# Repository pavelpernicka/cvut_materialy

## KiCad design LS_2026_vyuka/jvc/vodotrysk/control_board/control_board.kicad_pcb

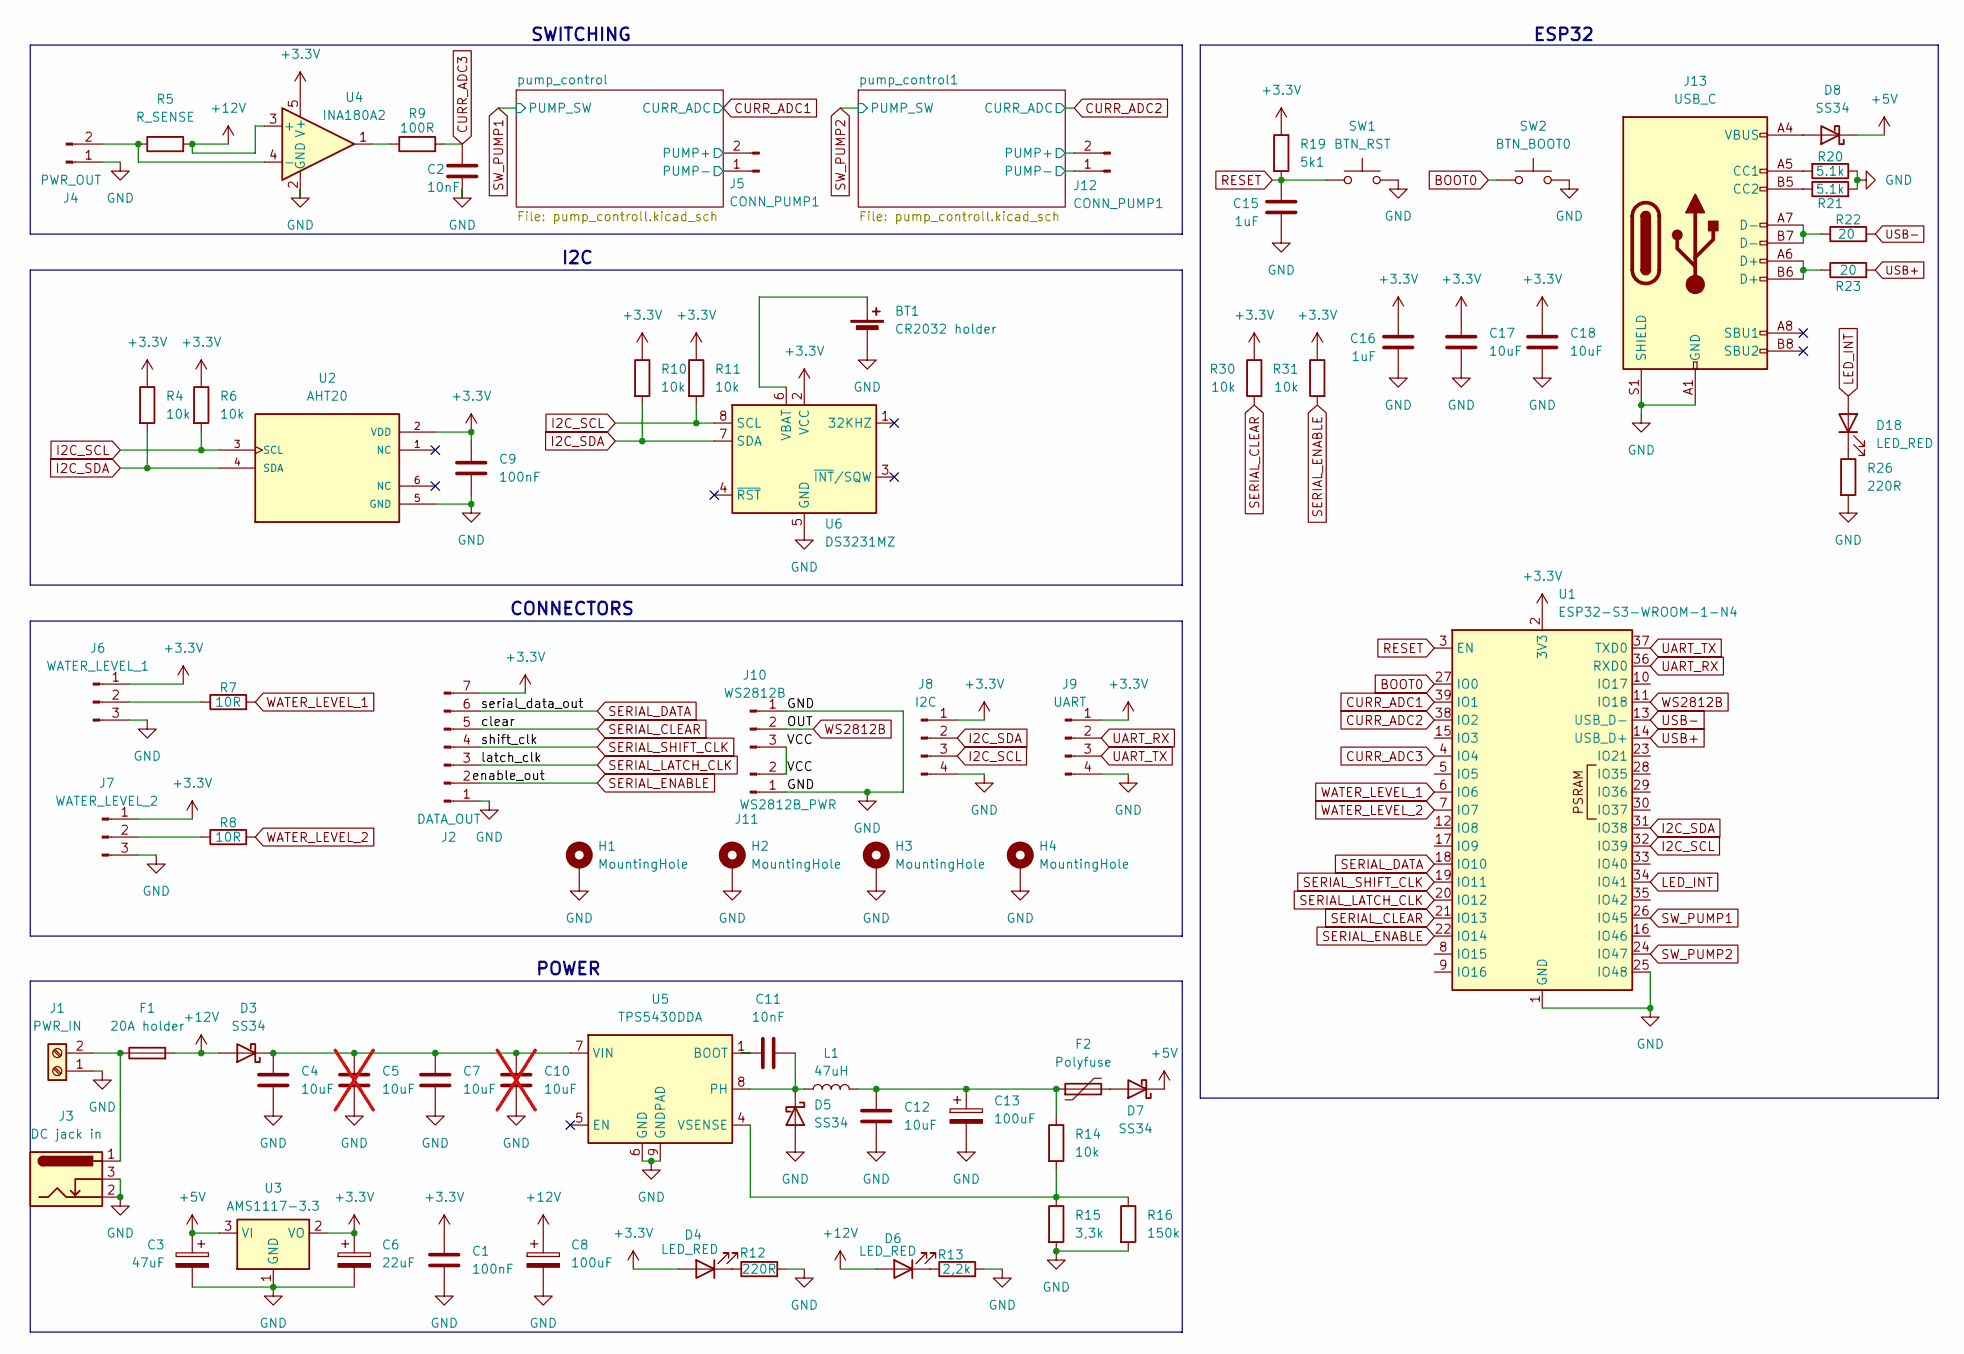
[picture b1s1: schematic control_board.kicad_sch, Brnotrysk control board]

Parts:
BT1: CR2032 holder; BatteryHolder_MYOUNG_BS-07-A1BJ001_CR2032; LCSC C5365915
C1, C9: 100nF; C_0805_2012Metric; LCSC C49678
C2, C11: 10nF; C_0805_2012Metric; LCSC C1710
C3: 47uF; C_0805_2012Metric; LCSC C16780
C4, C7, C12, C17, C18: 10uF; C_0805_2012Metric; LCSC C440198
C5, C10: 10uF; C_0805_2012Metric; LCSC C440198; not fitted
C6: 22uF; C_0805_2012Metric; LCSC C45783
C8, C13: 100uF; C_Radial_D10.0mm_H20.0mm_P5.00mm
C15, C16: 1uF; C_0805_2012Metric; LCSC C28323
D3, D5, D7, D8: SS34; D_SMA; LCSC C8678
D4, D6, D18: LED_RED; LED_0805_2012Metric_Pad1.15x1.40mm_HandSolder; LCSC C84256
F1: 20A holder; fuse_holder
F2: Polyfuse; Fuse_0805_2012Metric_Pad1.15x1.40mm_HandSolder
H1, H2, H3, H4: MountingHole; MountingHole_2.2mm_M2_Pad_Via
J1: PWR_IN; TerminalBlock_MaiXu_MX126-5.0-02P_1x02_P5.00mm
J2: DATA_OUT; dataconn
J3: DC jack in; BarrelJack_Wuerth_6941xx301002
J4: PWR_OUT; pwrconn
J5, J12: CONN_PUMP1; pwrconn
J6: WATER_LEVEL_1; sensorconn
J7: WATER_LEVEL_2; sensorconn
J8: I2C; PinHeader_1x04_P2.54mm_Vertical
J9: UART; PinHeader_1x04_P2.54mm_Vertical
J10: WS2812B; sensorconn
J11: WS2812B_PWR; pwrconn
J13: USB_C; USB_C_Receptacle_HCTL_HC-TYPE-C-16P-01A; LCSC C2894897
L1: 47uH; L_10.4x10.4_H4.8; LCSC C9934
R4, R6, R10, R11, R14, R30, R31: 10k; R_0805_2012Metric; LCSC C17414
R5: R_SENSE; R_4020_10251Metric_Pad1.65x5.30mm_HandSolder; LCSC C4944105
R7, R8: 10R; R_0805_2012Metric; LCSC C17415
R9: 100R; R_0805_2012Metric; LCSC C17408
R12, R26: 220R; R_0805_2012Metric; LCSC C17557
R13: 2,2k; R_0805_2012Metric; LCSC C17520
R15: 3,3k; R_0805_2012Metric; LCSC C26010
R16: 150k; R_0805_2012Metric; LCSC C17470
R19: 5k1; R_0805_2012Metric; LCSC C27834
R20, R21: 5.1k; R_0603_1608Metric; LCSC C23186
R22, R23: 20; R_0603_1608Metric; LCSC C22950
SW1: BTN_RST; SW_SPST_SKQG_WithStem; LCSC C318884
SW2: BTN_BOOT0; SW_SPST_SKQG_WithStem; LCSC C318884
U1: ESP32-S3-WROOM-1-N4; ESP32-S3-WROOM-1; LCSC C2913197
U2: AHT20; LCSC C3012622
U3: AMS1117-3.3; SOT-223-3_TabPin2; LCSC C6186
U4: INA180A2; SOT-23-5; LCSC C116203
U5: TPS5430DDA; TI_SO-PowerPAD-8_ThermalVias; LCSC C9864
U6: DS3231MZ; SOIC-8_3.9x4.9mm_P1.27mm; LCSC C107410

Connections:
+3.3V: C1.1, C6.1, C9.1, C16.1, C17.1, C18.1, D4.2 (A), J2.7, J6.1, J7.1, J8.1, J9.1, R4.1, R6.1, R10.1, R11.1, R19.1, R30.1, R31.1, U1.2 (3V3), U2.2 (VDD), U3.2 (VO), U4.5 (V+), U6.2 (VCC); also elsewhere on the board
+5V: C3.1, D7.1 (K), D8.1 (K), U3.3 (VI)
+12V: C8.1, D3.2 (A), D6.2 (A), F1.2, J5.2, J12.2, R5.2, U4.3 (+); also elsewhere on the board
/VCC: J10.3, J11.2
/pump_control1/PUMP-: J12.1; also elsewhere on the board
/pump_control/PUMP-: J5.1; also elsewhere on the board
BOOT0: SW2.1, U1.27 (IO0)
CURR_ADC1: U1.39 (IO1); also elsewhere on the board
CURR_ADC2: U1.38 (IO2); also elsewhere on the board
CURR_ADC3: C2.1, R9.2, U1.4 (IO4)
GND: BT1.2 (-), C1.2, C2.2, C3.2, C4.2, C5.2, C6.2, C7.2, C8.2, C9.2, C10.2, C12.2, C13.2, C15.2, C16.2, C17.2, C18.2, D5.2 (A), H1.1, H2.1, H3.1, H4.1, J1.1, J2.1, J3.2, J3.3, J4.1, J6.3, J7.3, J8.4, J9.4, J10.1, J11.1, J13.A1 (GND), J13.A12 (GND), J13.B1 (GND), J13.B12 (GND), J13.S1 (SHIELD), R12.2, R13.2, R15.2, R16.2, R20.1, R21.2, R26.2, SW1.2, SW2.2, U1.1 (GND), U1.25 (IO48), U1.40 (GND), U1.41 (GND), U2.5 (GND), U3.1 (GND), U4.2 (GND), U5.6 (GND), U5.9 (GNDPAD), U6.5 (GND); also elsewhere on the board
I2C_SCL: J8.3, R6.2, R11.2, U1.32 (IO39), U2.3 (SCL), U6.8 (SCL)
I2C_SDA: J8.2, R4.2, R10.2, U1.31 (IO38), U2.4 (SDA), U6.7 (SDA)
LED_INT: D18.2 (A), U1.34 (IO41)
unnamed: BT1.1 (+), U6.6 (VBAT)
unnamed: C12.1, C13.1, F2.1, L1.2, R14.1
unnamed: C4.1, C5.1, C7.1, C10.1, D3.1 (K), U5.7 (VIN)
unnamed: D4.1 (K), R12.1
unnamed: C11.2, D5.1 (K), L1.1, U5.8 (PH)
unnamed: D6.1 (K), R13.1
unnamed: D7.2 (A), F2.2
unnamed: D8.2 (A), J13.A4 (VBUS), J13.A9 (VBUS), J13.B4 (VBUS), J13.B9 (VBUS)
unnamed: D18.1 (K), R26.1
unnamed: F1.1, J1.2, J3.1
unnamed: J4.2, R5.1, U4.4 (-)
unnamed: J6.2, R7.1
unnamed: J7.2, R8.1
unnamed: J13.A5 (CC1), R20.2
unnamed: J13.B5 (CC2), R21.1
unnamed: J13.A6 (D+), J13.B6 (D+), R23.1
unnamed: J13.A7 (D-), J13.B7 (D-), R22.1
unnamed: R9.1, U4.1
unnamed: C11.1, U5.1 (BOOT)
unnamed: R14.2, R15.1, R16.1, U5.4 (VSENSE)
RESET: C15.1, R19.2, SW1.1, U1.3 (EN)
SERIAL_CLEAR: J2.5, R30.2, U1.21 (IO13)
SERIAL_DATA: J2.6, U1.18 (IO10)
SERIAL_ENABLE: J2.2, R31.2, U1.22 (IO14)
SERIAL_LATCH_CLK: J2.3, U1.20 (IO12)
SERIAL_SHIFT_CLK: J2.4, U1.19 (IO11)
SW_PUMP1: U1.26 (IO45); also elsewhere on the board
SW_PUMP2: U1.24 (IO47); also elsewhere on the board
UART_RX: J9.2, U1.36 (RXD0)
UART_TX: J9.3, U1.37 (TXD0)
USB+: R23.2, U1.14 (USB_D+)
USB-: R22.2, U1.13 (USB_D-)
WATER_LEVEL_1: R7.2, U1.6 (IO6)
WATER_LEVEL_2: R8.2, U1.7 (IO7)
WS2812B: J10.2, U1.11 (IO18)

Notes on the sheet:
SWITCHING
ESP32
I2C
CONNECTORS
POWER

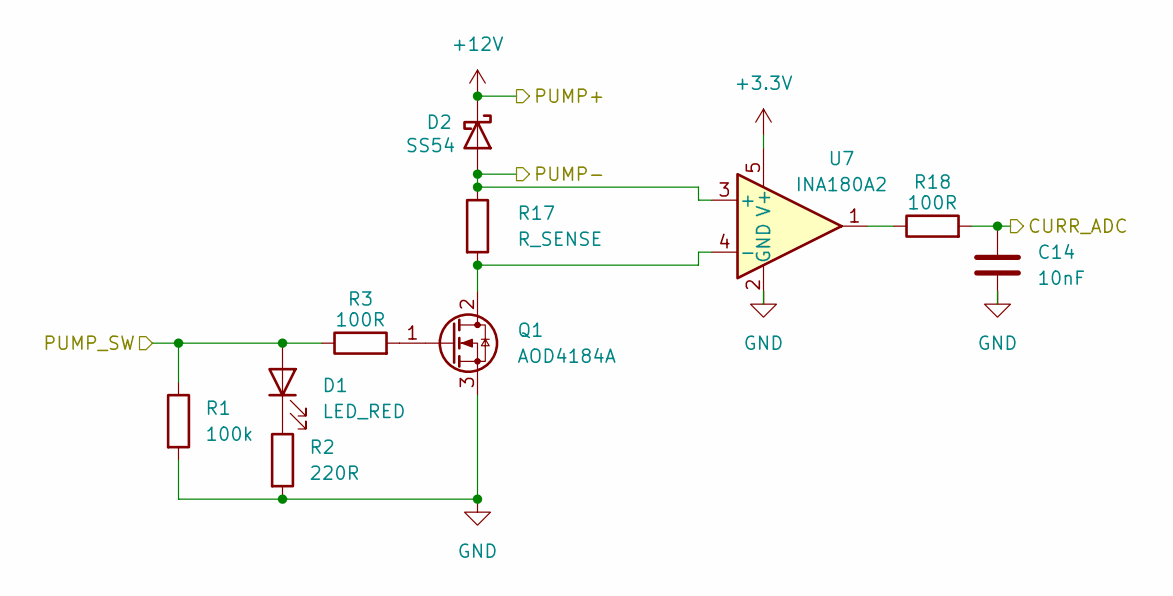
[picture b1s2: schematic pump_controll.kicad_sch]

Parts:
C14: 10nF; C_0805_2012Metric; LCSC C1710
D1: LED_RED; LED_0805_2012Metric_Pad1.15x1.40mm_HandSolder; LCSC C84256
D2: SS54; D_SMA_Handsoldering; LCSC C22452
Q1: AOD4184A; TO-252-2; LCSC C5370959
R1: 100k; R_0805_2012Metric; LCSC C149504
R2: 220R; R_0805_2012Metric; LCSC C17557
R3, R18: 100R; R_0805_2012Metric; LCSC C17408
R17: R_SENSE; R_2512_6332Metric_Pad1.40x3.35mm_HandSolder; LCSC C5121057
U7: INA180A2; SOT-23-5; LCSC C116203

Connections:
+3.3V: U7.5 (V+); also elsewhere on the board
+12V: D2.1 (K); also elsewhere on the board
/pump_control/PUMP-: D2.2 (A), R17.1, U7.3 (+); also elsewhere on the board
CURR_ADC1: C14.1, R18.2; also elsewhere on the board
GND: C14.2, Q1.3 (S), R1.2, R2.2, U7.2 (GND); also elsewhere on the board
unnamed: D1.1 (K), R2.1
unnamed: Q1.2 (D), R17.2, U7.4 (-)
unnamed: Q1.1 (G), R3.2
unnamed: R18.1, U7.1
SW_PUMP1: D1.2 (A), R1.1, R3.1; also elsewhere on the board

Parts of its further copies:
C19: 10nF; C_0805_2012Metric; LCSC C1710
D9: LED_RED; LED_0805_2012Metric_Pad1.15x1.40mm_HandSolder; LCSC C84256
D10: SS54; D_SMA_Handsoldering; LCSC C22452
Q2: AOD4184A; TO-252-2; LCSC C5370959
R24: 100k; R_0805_2012Metric; LCSC C149504
R25: 220R; R_0805_2012Metric; LCSC C17557
R27, R29: 100R; R_0805_2012Metric; LCSC C17408
R28: R_SENSE; R_2512_6332Metric_Pad1.40x3.35mm_HandSolder; LCSC C5121057
U8: INA180A2; SOT-23-5; LCSC C116203

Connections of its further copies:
+3.3V: U8.5 (V+); also elsewhere on the board
+12V: D10.1 (K); also elsewhere on the board
/pump_control1/PUMP-: D10.2 (A), R28.1, U8.3 (+); also elsewhere on the board
CURR_ADC2: C19.1, R29.2; also elsewhere on the board
GND: C19.2, Q2.3 (S), R24.2, R25.2, U8.2 (GND); also elsewhere on the board
unnamed: D9.1 (K), R25.1
unnamed: Q2.2 (D), R28.2, U8.4 (-)
unnamed: Q2.1 (G), R27.2
unnamed: R29.1, U8.1
SW_PUMP2: D9.2 (A), R24.1, R27.1; also elsewhere on the board

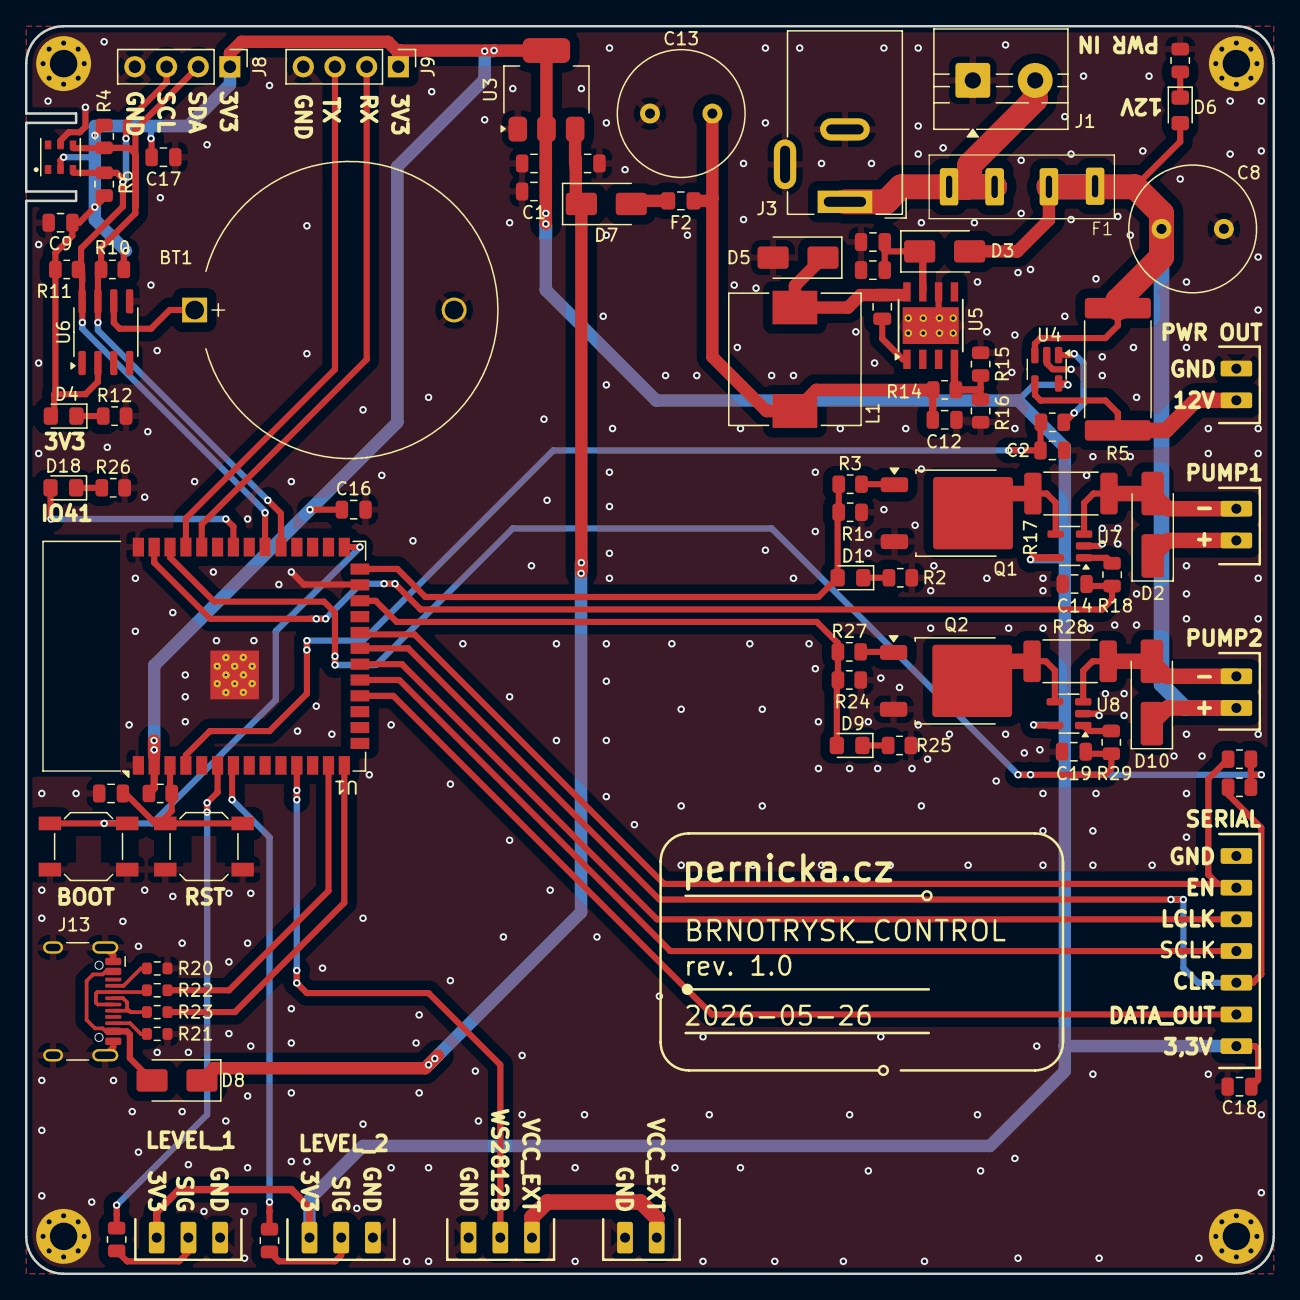
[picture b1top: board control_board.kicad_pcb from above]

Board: 2 copper layers, 100.0 x 100.0 mm, 92 parts (0 on the bottom side), 57 nets.

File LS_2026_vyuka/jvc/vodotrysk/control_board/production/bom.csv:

Designator,Footprint,Quantity,Value,LCSC Part #
BT1,BatteryHolder_MYOUNG_BS-07-A1BJ001_CR2032,1,CR2032 holder,C5365915
"C1, C9",0805,2,100nF,C49678
"C11, C14, C19, C2",0805,4,10nF,C1710
"C12, C17, C18, C4, C7",0805,5,10uF,C440198
"C13, C8",C_Radial_D10.0mm_H20.0mm_P5.00mm,2,100uF,
"C15, C16",0805,2,1uF,C28323
C3,0805,1,47uF,C16780
C6,0805,1,22uF,C45783
"D1, D18, D4, D6, D9",0805,5,LED_RED,C84256
"D10, D2",D_SMA_Handsoldering,2,SS54,C22452
"D3, D5, D7, D8",D_SMA,4,SS34,C8678
F1,fuse_holder,1,20A holder,
F2,0805,1,Polyfuse,
J1,TerminalBlock_MaiXu_MX126-5.0-02P_1x02_P5.00mm,1,PWR_IN,
J10,sensorconn,1,WS2812B,
J11,pwrconn,1,WS2812B_PWR,
"J12, J5",pwrconn,2,CONN_PUMP1,
J13,USB_C_Receptacle_HCTL_HC-TYPE-C-16P-01A,1,USB_C,C2894897
J2,dataconn,1,DATA_OUT,
J3,BarrelJack_Wuerth_6941xx301002,1,DC jack in,
J4,pwrconn,1,PWR_OUT,
J6,sensorconn,1,WATER_LEVEL_1,
J7,sensorconn,1,WATER_LEVEL_2,
J8,PinHeader_1x04_P2.54mm_Vertical,1,I2C,
J9,PinHeader_1x04_P2.54mm_Vertical,1,UART,
L1,L_10.4x10.4_H4.8,1,47uH,C9934
"Q1, Q2",TO-252-2,2,AOD4184A,C5370959
"R1, R24",0805,2,100k,C149504
"R10, R11, R14, R30, R31, R4, R6",0805,7,10k,C17414
"R12, R2, R25, R26",0805,4,220R,C17557
R13,0805,1,"2,2k",C17520
R15,0805,1,"3,3k",C26010
R16,0805,1,150k,C17470
"R17, R28",2512,2,R_SENSE,C5121057
"R18, R27, R29, R3, R9",0805,5,100R,C17408
R19,0805,1,5k1,C27834
"R20, R21",0603,2,5.1k,C23186
"R22, R23",0603,2,20,C22950
R5,4020,1,R_SENSE,C4944105
"R7, R8",0805,2,10R,C17415
SW1,SW_SPST_SKQG_WithStem,1,BTN_RST,C318884
SW2,SW_SPST_SKQG_WithStem,1,BTN_BOOT0,C318884
U1,ESP32-S3-WROOM-1,1,ESP32-S3-WROOM-1-N4,C2913197 
U2,AHT20,1,AHT20,C3012622
U3,SOT-223-3_TabPin2,1,AMS1117-3.3,C6186 
"U4, U7, U8",SOT-23-5,3,INA180A2,C116203 
U5,TI_SO-PowerPAD-8_ThermalVias,1,TPS5430DDA,C9864
U6,SOIC-8_3.9x4.9mm_P1.27mm,1,DS3231MZ,C107410

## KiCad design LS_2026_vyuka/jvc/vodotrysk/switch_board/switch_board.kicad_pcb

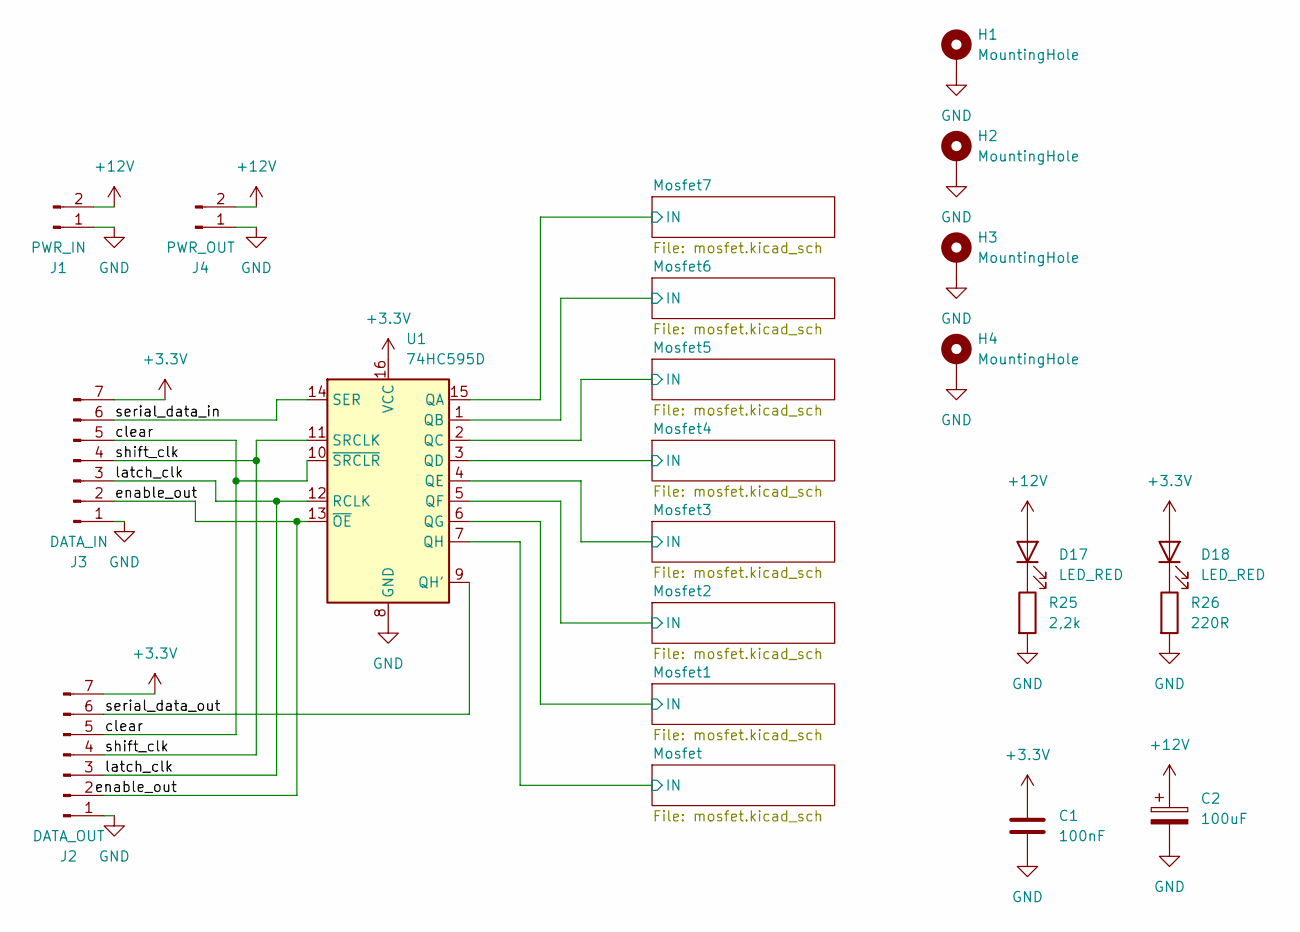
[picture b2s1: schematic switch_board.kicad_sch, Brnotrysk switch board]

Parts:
C1: 100nF; C_0805_2012Metric; LCSC C49678
C2: 100uF
D17, D18: LED_RED; LED_0805_2012Metric_Pad1.15x1.40mm_HandSolder; LCSC C84256
H1, H2, H3, H4: MountingHole; MountingHole_2.2mm_M2_Pad_Via
J1: PWR_IN; pwrconn
J2: DATA_OUT; dataconn
J3: DATA_IN; dataconn
J4: PWR_OUT; pwrconn
R25: 2,2k; R_0805_2012Metric; LCSC C17520
R26: 220R; R_0805_2012Metric; LCSC C17557
U1: 74HC595D; SOIC-16_3.9x9.9mm_P1.27mm; LCSC C5947

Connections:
+3.3V: C1.1, D18.2 (A), J2.7, J3.7, U1.16 (VCC)
+12V: C2.1, D17.2 (A), J1.2, J4.2; also elsewhere on the board
/Mosfet1/IN: U1.6 (QG); also elsewhere on the board
/Mosfet2/IN: U1.5 (QF); also elsewhere on the board
/Mosfet3/IN: U1.4 (QE); also elsewhere on the board
/Mosfet4/IN: U1.3 (QD); also elsewhere on the board
/Mosfet5/IN: U1.2 (QC); also elsewhere on the board
/Mosfet6/IN: U1.1 (QB); also elsewhere on the board
/Mosfet7/IN: U1.15 (QA); also elsewhere on the board
/Mosfet/IN: U1.7 (QH); also elsewhere on the board
/clear: J2.5, J3.5, U1.10 (~SRCLR)
/enable_out: J2.2, J3.2, U1.13 (~OE)
/latch_clk: J2.3, J3.3, U1.12 (RCLK)
/serial_data_in: J3.6, U1.14 (SER)
/serial_data_out: J2.6, U1.9 (QH')
/shift_clk: J2.4, J3.4, U1.11 (SRCLK)
GND: C1.2, C2.2, H1.1, H2.1, H3.1, H4.1, J1.1, J2.1, J3.1, J4.1, R25.2, R26.2, U1.8 (GND); also elsewhere on the board
unnamed: D17.1 (K), R25.1
unnamed: D18.1 (K), R26.1

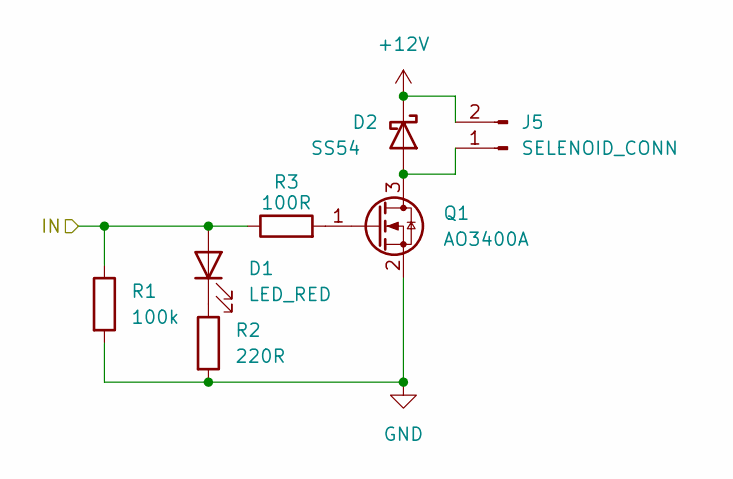
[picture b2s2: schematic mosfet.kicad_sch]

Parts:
D1: LED_RED; LED_0805_2012Metric_Pad1.15x1.40mm_HandSolder; LCSC C84256
D2: SS54; D_SMA_Handsoldering; LCSC C22452
J5: SELENOID_CONN; pwrconn
Q1: AO3400A; SOT-23; LCSC C20917
R1: 100k; R_0805_2012Metric; LCSC C149504
R2: 220R; R_0805_2012Metric; LCSC C17557
R3: 100R; R_0805_2012Metric; LCSC C17408

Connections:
+12V: D2.1 (K), J5.2; also elsewhere on the board
/Mosfet/IN: D1.2 (A), R1.1, R3.1; also elsewhere on the board
GND: Q1.2 (S), R1.2, R2.2; also elsewhere on the board
unnamed: D1.1 (K), R2.1
unnamed: D2.2 (A), J5.1, Q1.3 (D)
unnamed: Q1.1 (G), R3.2

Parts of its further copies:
D3, D5, D7, D9, D11, D13, D15: LED_RED; LED_0805_2012Metric_Pad1.15x1.40mm_HandSolder; LCSC C84256
D4, D6, D8, D10, D12, D14, D16: SS54; D_SMA_Handsoldering; LCSC C22452
J6, J7, J8, J9, J10, J11, J12: SELENOID_CONN; pwrconn
Q2, Q3, Q4, Q5, Q6, Q7, Q8: AO3400A; SOT-23; LCSC C20917
R4, R7, R10, R13, R16, R19, R22: 100k; R_0805_2012Metric; LCSC C149504
R5, R8, R11, R14, R17, R20, R23: 220R; R_0805_2012Metric; LCSC C17557
R6, R9, R12, R15, R18, R21, R24: 100R; R_0805_2012Metric; LCSC C17408

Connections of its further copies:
+12V: D4.1 (K), D6.1 (K), D8.1 (K), D10.1 (K), D12.1 (K), D14.1 (K), D16.1 (K), J6.2, J7.2, J8.2, J9.2, J10.2, J11.2, J12.2; also elsewhere on the board
/Mosfet1/IN: D3.2 (A), R4.1, R6.1; also elsewhere on the board
/Mosfet2/IN: D5.2 (A), R7.1, R9.1; also elsewhere on the board
/Mosfet3/IN: D7.2 (A), R10.1, R12.1; also elsewhere on the board
/Mosfet4/IN: D9.2 (A), R13.1, R15.1; also elsewhere on the board
/Mosfet5/IN: D11.2 (A), R16.1, R18.1; also elsewhere on the board
/Mosfet6/IN: D13.2 (A), R19.1, R21.1; also elsewhere on the board
/Mosfet7/IN: D15.2 (A), R22.1, R24.1; also elsewhere on the board
GND: Q2.2 (S), Q3.2 (S), Q4.2 (S), Q5.2 (S), Q6.2 (S), Q7.2 (S), Q8.2 (S), R4.2, R5.2, R7.2, R8.2, R10.2, R11.2, R13.2, R14.2, R16.2, R17.2, R19.2, R20.2, R22.2, R23.2; also elsewhere on the board
unnamed: D3.1 (K), R5.1
unnamed: D4.2 (A), J6.1, Q2.3 (D)
unnamed: D5.1 (K), R8.1
unnamed: D6.2 (A), J7.1, Q3.3 (D)
unnamed: D7.1 (K), R11.1
unnamed: D8.2 (A), J8.1, Q4.3 (D)
unnamed: D9.1 (K), R14.1
unnamed: D10.2 (A), J9.1, Q5.3 (D)
unnamed: D11.1 (K), R17.1
unnamed: D12.2 (A), J10.1, Q6.3 (D)
unnamed: D13.1 (K), R20.1
unnamed: D14.2 (A), J11.1, Q7.3 (D)
unnamed: D15.1 (K), R23.1
unnamed: D16.2 (A), J12.1, Q8.3 (D)
unnamed: Q2.1 (G), R6.2
unnamed: Q3.1 (G), R9.2
unnamed: Q4.1 (G), R12.2
unnamed: Q5.1 (G), R15.2
unnamed: Q6.1 (G), R18.2
unnamed: Q7.1 (G), R21.2
unnamed: Q8.1 (G), R24.2

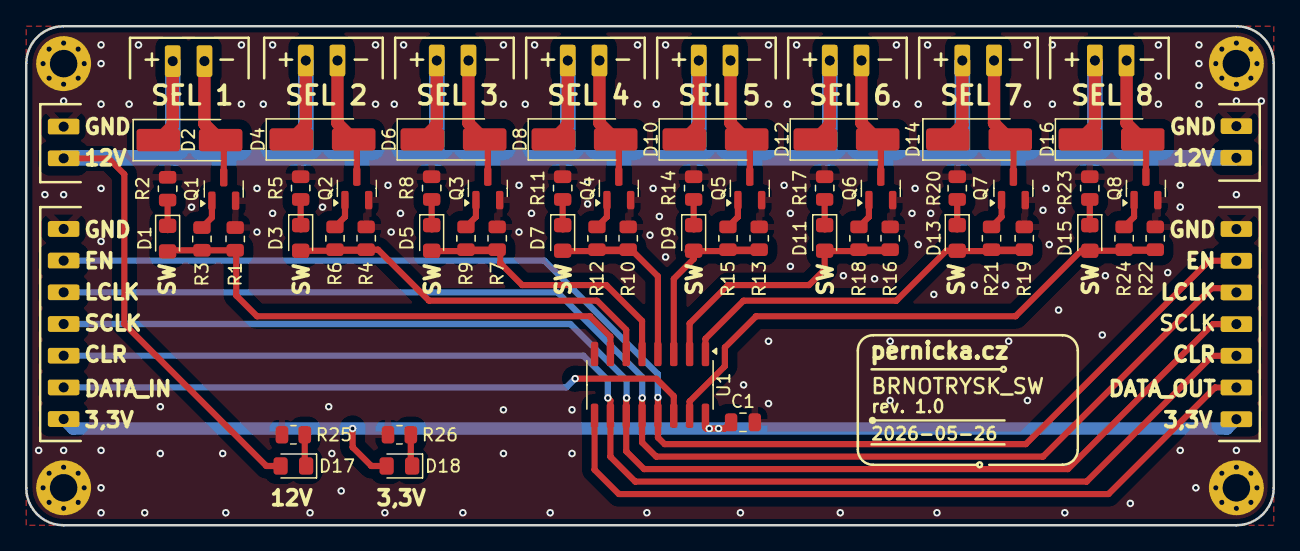
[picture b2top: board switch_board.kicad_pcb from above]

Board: 2 copper layers, 100.0 x 40.0 mm, 70 parts (0 on the bottom side), 43 nets.

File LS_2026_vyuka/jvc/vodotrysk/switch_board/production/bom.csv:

Designator,Footprint,Quantity,Value,LCSC Part #
C1,0805,1,100nF,C49678
"D1, D11, D13, D15, D17, D18, D3, D5, D7, D9",0805,10,LED_RED,C84256
"D10, D12, D14, D16, D2, D4, D6, D8",D_SMA_Handsoldering,8,SS54,C22452
J1,pwrconn,1,PWR_IN,
"J10, J11, J12, J5, J6, J7, J8, J9",pwrconn,8,SELENOID_CONN,
J2,dataconn,1,DATA_OUT,
J3,dataconn,1,DATA_IN,
J4,pwrconn,1,PWR_OUT,
"Q1, Q2, Q3, Q4, Q5, Q6, Q7, Q8",SOT-23,8,AO3400A,C20917
"R1, R10, R13, R16, R19, R22, R4, R7",0805,8,100k,C149504
"R11, R14, R17, R2, R20, R23, R26, R5, R8",0805,9,220R,C17557
"R12, R15, R18, R21, R24, R3, R6, R9",0805,8,100R,C17408
R25,0805,1,"2,2k",C17520
U1,SOIC-16_3.9x9.9mm_P1.27mm,1,74HC595D,C5947

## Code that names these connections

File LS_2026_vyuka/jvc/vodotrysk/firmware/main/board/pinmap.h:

#pragma once

#define PIN_USB_D_MINUS 19
#define PIN_USB_D_PLUS 20

#define PIN_SR_DATA 10
#define PIN_SR_SHIFT_CLK 11
#define PIN_SR_LATCH_CLK 12
#define PIN_SR_CLEAR 13
#define PIN_SR_ENABLE 14

#define PIN_I2C_SDA 38
#define PIN_I2C_SCL 39

#define PIN_WS2812B 18
#define PIN_LED_INT 41

#define PIN_WATER_LEVEL_1 6
#define PIN_WATER_LEVEL_2 7

#define PIN_CURR_ADC1 1
#define PIN_CURR_ADC2 2
#define PIN_CURR_ADC3 4

#define PIN_SW_PUMP1_RECOMMENDED 15
#define PIN_SW_PUMP1_LEGACY 45
#define PIN_SW_PUMP2 47

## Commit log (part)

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2025-01-20 fixed download from hedgedoc
2025-01-20 LAG materials
2025-01-20 LGR materials
2025-01-21 LGR zkouska stuff
2025-01-28 updated logic and graphs notes
2025-01-29 ZS2024-robots tuned pid
2025-01-29 LGR flashcards
2025-03-24 Added summer semester
2025-03-24 added JAP lesson materials
2025-04-29 added physics 1 labs
2025-04-29 added programming in C homeworks
2025-04-29 added ma2 semestral test overview
2025-05-22 Summer semester
2025-05-22 Summer 2025 KUI remove pycache
2025-05-22 Summer 2025 notes
2025-10-20 Phisics 2
2025-11-21 Added FY2/lab06
2025-12-06 Fixed fy_lab06 typo
2025-12-06 Added FY2 HWs
2025-12-06 Complex analysis transformations list
2026-01-15 FY2 laboratories
2026-01-15 FEN laboratories
2026-01-15 FEN - Plasmatic focus lab
2026-02-26 ari + jvc
2026-02-26 jvc krabice
2026-03-05 Beer day presentation -PRE
2026-03-05 Sensors and measurements - lab 4
2026-03-05 ARI - homework 2
2026-03-18 SME labs
2026-03-18 ARI HW04
2026-03-20 PRE vynález
2026-04-10 PRE - hudba
2026-04-10 Older JVC stuff
2026-04-10 SME Lab02
2026-04-10 SME Lab03
2026-04-10 SME Lab09
2026-04-10 SME Lab06
2026-04-10 JVC vodotrysk
2026-04-10 LPE folder
2026-04-12 jvc rs4 firmware
2026-04-14 RS41 firmware
2026-04-16 fixed lab06
2026-04-16 SME lab10
2026-04-19 SME lab11
2026-04-22 JVC CAM
2026-04-22 LPE magnetometr+oled
2026-04-22 SME lab12 priprava
2026-04-22 LSP projects until task3
2026-04-22 LPE motors docs
2026-04-27 SME lab12
2026-04-27 Initial state of LSP task 4
2026-04-27 JVC - projekt vitraze
2026-04-28 JVC vitraz podstavec
2026-04-29 Preparation for SME lab07
2026-05-05 PRE radary
2026-05-05 PRE gamma
2026-05-05 JVC final project material list
2026-05-05 JVC stroj
2026-05-05 PRE final pdf
2026-05-05 SME lab07 final
2026-05-05 SME lab08 home preparation
2026-05-22 LSP task 4 full
2026-05-22 JVC odlevani
2026-05-22 JVC chlastostroj
2026-05-22 JVC vodotrysk mechanical parts
2026-05-31 JVC vodotrysk construction files
2026-06-04 updated mechanical + firmware
